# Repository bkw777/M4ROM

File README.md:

# M4ROM

Virtual 27C256 rom x 4 to fit Molex 78805 socket

This is a version of [Teeprom and Meeprom](https://github.com/bkw777/Teeprom) that uses a 128k 29F010 flash instead of a 32k 28C256 eeprom.

The advantages over the original Teeprom are:  
* The flash chip is cheaper and more readily available than the eeprom.  
* The programming adapter is cheaper to buy and simpler to use than the soic test clip.
* Holds four 32k rom images instead of one.  

The disadvantages are:  
* The board has more parts and is more difficult to solder.

There are two almost identical versions supporting two commonly needed pinouts:  
'''M4ROM_TANDY''' is only for TANDY 100, 102, & 200, same as Teeprom.  
'''M4ROM_27256''' is for everything else, same as Meeprom. (TANDY 600, Epson PX-4 & PX-8, Kyotronic KC-85)

All parts other than the PCB are the same for both versions.  
The difference is only in the pinout of the castellated edge connectors. TANDY 100, 102, & 200 have a non-standard pinout. The 27256 version provides a standard 27C256 or 32Kx8 parallel mask rom pinout.

The same programming adapter is used for both.

<!--  -->

### Parts
[TANDY PCB @ PCBWAY](https://www.pcbway.com/project/shareproject/4ROM_100_multi_option_rom_module_for_TRS_80_Model_100_102_200_93cfa6c8.html)

[27256 PCB @ PCBWAY](https://www.pcbway.com/project/shareproject/4ROM_78802_714ecf32.html)

[Carrier @ PCBWAY](https://www.pcbway.com/project/shareproject/Molex_7880x_28_PCB_Carrier_9419cd9c.html)

[BOM @ DigiKey](https://www.digikey.com/short/z1j1wwrj)

[Programming Adapter PCB @ PCBWAY](https://www.pcbway.com/project/shareproject/4ROM_Programming_Adapter_fc156337.html)

[Programming Adapter BOM @ DigiKey](https://www.digikey.com/short/drp9qj7w)

When ordering the PCB:  
* Min Tracks/Spaces: 6mil  
  The order page sometimes auto-selects 5mil which is more expensive, but there are no such thin traces or spaces.  
* Copper Finish: ENIG    (not the programming adapter)  
  So the castellated edge contacts and programming adapter contacts are gold plated.

# Programming the chip  
First a few notes,  
Do a full chip erase once first, seperately from writing the banks.  
Disable the usual default automatic erase-first when writing.  
Each bank can only be written once per erase. To over-write a bank, you have to erase the whole chip and write all 4 banks again.  

Procedure:  
1 Put the programming adapter into a programmer.  
2 Remove the M4ROM PCB from the carrier and connect it to the programming adapter by the center pins. DON'T try to push the PCB all the way down. It should be stiff right away while the board is still near the top of the pins.  
3 [Test pin connections](#test-the-pin-connections). Pin-test function in the programmer, it should say bad contact on pins 2 & 3, and nothing else.  
4 [Erase the whole chip](#erase-the-whole-chip).  
5 Select the desired bank number with the slide switch on the M4ROM.  
6 [Write a single 32K rom image](#write-one-bank). Disable erase-first.  
7 Repeat 5 & 6 for the remaining banks.

The chip may be re-written as many times as you want, but once data has been written to a given bank, that bank can not be written again without erasing the whole chip again first.  

## Example
The following is using a TL-866II+ programmer and the open source [minipro](https://gitlab.com/DavidGriffith/minipro) software.  

### Test the pin connections  
It should say bad contact on pins 2 and 3, and nothing else.  
```
$ minipro --device 'SST39SF010A' --pin_check
Found TL866II+ 04.2.132 (0x284)
Bad contact on pin:2
Bad contact on pin:3
$
```

If you see anything else, try pushing the PCB down slightly harder. It still shouldn't go anywhere near all the way down, and don't try to force it, but the harder you push down the harder the pins wedge in the holes.

The way the programming adapter connection works is the holes are almost the exact size of the pins, and the holes are spaced closer together than the pins, so the pins bind up tighter the further down you push the PCB. As the PCB slides down, the pins are pushed sideways and lean over, and make contact at both the bottom and top edges of the PCB.

### Read one bank
The actual chip is a 128K part like 39SF010, but we can't read 128K we can only read 32K because not all of the address lines are connected from the chip to the programmer.  
The most convenient way to make the programmer read less than 128K is to tell the programmer to read a 32K chip that has the same kind of read cycle as the actual chip, like AM28F256.

```
$ minipro --device 'AM28F256' --skip_id --read bank1.bin
Found TL866II+ 04.2.132 (0x284)
Device code: 19339229
Serial code: XYG0VZ54DQ4VCC53WFWZ
USB speed: 12Mbps (USB 1.1)
WARNING: skipping Chip ID test
Reading Code...  0.30Sec  OK
$ 
```

### Erase the whole chip
The chip must be erased once before writing any banks, and then the normal erase-before-write must be suppressed when writing the individual banks.

Once the whole chip is erased, each bank may be written once.

It's not possible to erase a single bank, only the whole chip, so in order to re-write a bank that isn't currently blank, the whole chip must be erased again.

```
$ minipro --device 'SST39SF010A' --unprotect --erase
Found TL866II+ 04.2.132 (0x284)
Chip ID: 0xBFB5  OK
Erasing... 0.40Sec OK
$
```

### Write one bank  
For writing unlike reading we have to tell the programmer the correct actual device instead of some 32K device, but unlike for reading we do have an option to write less than 128K.  
Disable the automatic erase-before-write.  
Enable the software write-protection after writing. This protects against corruption during power-down & power-up transitions.  
The rom image file should be 32K bytes.

```
$ minipro --device 'SST39SF010A' --unprotect --protect --no_size_error --skip_erase --write TSD101.BX
Found TL866II+ 04.2.132 (0x284)
Device code: 19339229
Serial code: XYG0VZ54DQ4VCC53WFWZ
Chip ID: 0xBFB5  OK
Warning: Incorrect file size: 32768 (needed 131072)
Writing Code...  1.75Sec  OK
Reading Code...  0.25Sec  OK
Verification OK
```

# References
[Molex78802_Module](https://github.com/bkw777/Molex78802_Module)

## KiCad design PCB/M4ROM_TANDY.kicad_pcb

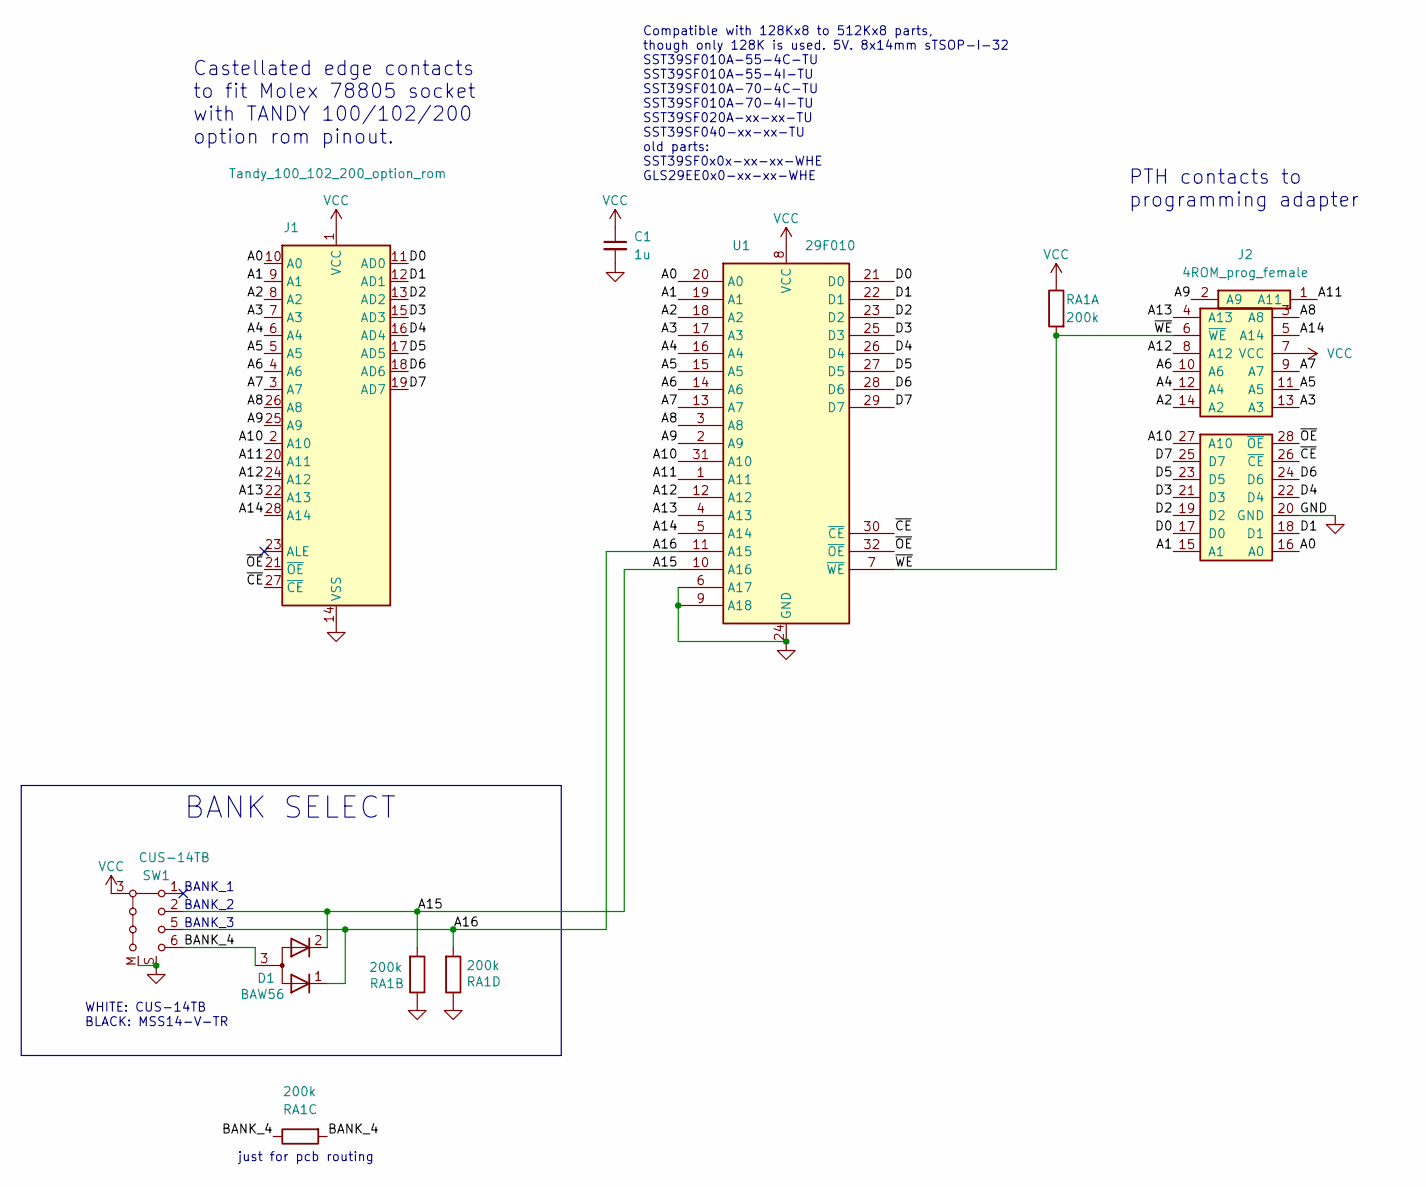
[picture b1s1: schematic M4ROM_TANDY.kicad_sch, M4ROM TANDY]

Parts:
C1: 1u; C_0805; MPN CL21B105KBFNNNE
D1: BAW56; SOT-23; MPN TBAW56,LM
J1: Tandy_100_102_200_option_rom; Molex78802_PCB_28
J2: 4ROM_prog_female
RA1: 200k; R_Array_Convex_4x0612; MPN YC164-JR-07200KL
SW1: CUS-14TB; SW_SP4T_CUS-14B - PTH; MPN CUS-14TB
U1: 29F010; TSOP32-14mm; MPN SST39SF010A-70-4C-TU

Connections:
/A0: J1.10 (A0), J2.16 (A0), U1.20 (A0)
/A1: J1.9 (A1), J2.15 (A1), U1.19 (A1)
/A2: J1.8 (A2), J2.14 (A2), U1.18 (A2)
/A3: J1.7 (A3), J2.13 (A3), U1.17 (A3)
/A4: J1.6 (A4), J2.12 (A4), U1.16 (A4)
/A5: J1.5 (A5), J2.11 (A5), U1.15 (A5)
/A6: J1.4 (A6), J2.10 (A6), U1.14 (A6)
/A7: J1.3 (A7), J2.9 (A7), U1.13 (A7)
/A8: J1.26 (A8), J2.3 (A8), U1.3 (A8)
/A9: J1.25 (A9), J2.2 (A9), U1.2 (A9)
/A10: J1.2 (A10), J2.27 (A10), U1.31 (A10)
/A11: J1.20 (A11), J2.1 (A11), U1.1 (A11)
/A12: J1.24 (A12), J2.8 (A12), U1.12 (A12)
/A13: J1.22 (A13), J2.4 (A13), U1.4 (A13)
/A14: J1.28 (A14), J2.5 (A14), U1.5 (A14)
/A15: D1.2 (K), RA1.2 (R2.1), SW1.2, U1.10 (A16)
/A16: D1.1 (K), RA1.4 (R4.1), SW1.5, U1.11 (A15)
/BANK_4: D1.3 (A), RA1.3 (R3.1), RA1.6 (R3.2), SW1.6
/D0: J1.11 (AD0), J2.17 (D0), U1.21 (D0)
/D1: J1.12 (AD1), J2.18 (D1), U1.22 (D1)
/D2: J1.13 (AD2), J2.19 (D2), U1.23 (D2)
/D3: J1.15 (AD3), J2.21 (D3), U1.25 (D3)
/D4: J1.16 (AD4), J2.22 (D4), U1.26 (D4)
/D5: J1.17 (AD5), J2.23 (D5), U1.27 (D5)
/D6: J1.18 (AD6), J2.24 (D6), U1.28 (D6)
/D7: J1.19 (AD7), J2.25 (D7), U1.29 (D7)
/~CE: J1.27 (~CE), J2.26 (~CE), U1.30 (~CE)
/~OE: J1.21 (~OE), J2.28 (~OE), U1.32 (~OE)
/~WE: J2.6 (~WE), RA1.1 (R1.1), U1.7 (~WE)
GND: C1.2, J1.14 (VSS), J2.20 (GND), RA1.5 (R4.2), RA1.7 (R2.2), SW1.M, SW1.S, U1.6 (A17), U1.9 (A18), U1.24 (GND)
VCC: C1.1, J1.1 (VCC), J2.7 (VCC), RA1.8 (R1.2), SW1.3 (C), SW1.4 (C), U1.8 (VCC)

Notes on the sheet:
BANK_3
WHITE: CUS-14TB BLACK: MSS14-V-TR
Castellated edge contacts to fit Molex 78805 socket with TANDY 100/102/200 option rom pinout.
BANK_1
just for pcb routing
BANK_2
BANK SELECT
PTH contacts to programming adapter
Compatible with 128Kx8 to 512Kx8 parts, though only 128K is used. 5V. 8x14mm sTSOP-I-32 SST39SF010A-55-4C-TU SST39SF010A-55-4I-TU SST39SF010A-70-4C-TU SST39SF010A-70-4I-TU SST39SF020A-xx-xx-TU SST39SF040-xx-xx-TU old parts: SST39SF0x0x-xx-xx-WHE GLS29EE0x0-xx-xx-WHE

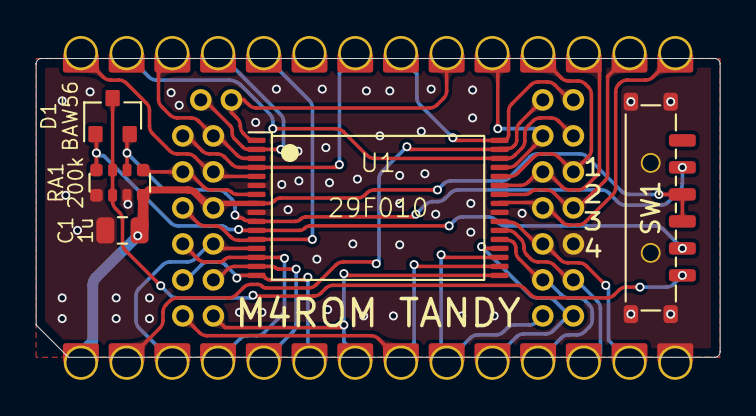
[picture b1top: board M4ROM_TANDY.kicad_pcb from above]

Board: 2 copper layers, 38.0 x 16.6 mm, 7 parts (0 on the bottom side), 31 nets.

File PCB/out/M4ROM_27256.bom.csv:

"Reference","Value","Datasheet","Footprint","Qty","DNP","MPN","Description"
"C1","1u","datasheets/CL21B105KBFNNNE.pdf","000_LOCAL:C_0805","1","","CL21B105KBFNNNE","CAP CER 1UF 16V+ 0805"
"D1","BAW56","datasheets/BAW56.PDF","000_LOCAL:SOT-23","1","","TBAW56,LM","Dual diode, common anode on pin 3"
"RA1","200k","datasheets/YC164.pdf","000_LOCAL:R_Array_Convex_4x0612","1","","YC164-JR-07200KL","RES ARRAY 4 x 200K isolated 1206 4x0612 convex"
"SW1","CUS-14TB","datasheets/cus.pdf","000_LOCAL:SW_SP4T_CUS-14B - PTH","1","","CUS-14TB","CUS-14TB Switch, 4 position, single pole 4 throw, 4 position switch, SP4T"
"U1","29F010","datasheets/29F040.pdf","000_LOCAL:TSOP32-14mm","1","","SST39SF010A-70-4C-TU","IC FLASH 128K-512Kx8 5V PARALLEL 32TSOP 8x14mm"

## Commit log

2023-12-31 fork 4ROM to it's own repo
2023-12-31 readme
2024-01-01 pcb polish
2024-01-01 improve some teardrops
2024-03-07 kicad 8
2025-02-21 MPN boms, centroids, and chip unavailability notes
2025-04-29 new flash part number
2025-09-18 readme digikey bom link had old flash part number
2025-10-06 readme. fillet tracks
2025-11-18 simpler diodes
2025-11-18 pics
2025-11-18 copper to edge 0.5mm

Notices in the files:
PCB/M4ROM_TANDY.kicad_pcb:
CC-BY-SA
